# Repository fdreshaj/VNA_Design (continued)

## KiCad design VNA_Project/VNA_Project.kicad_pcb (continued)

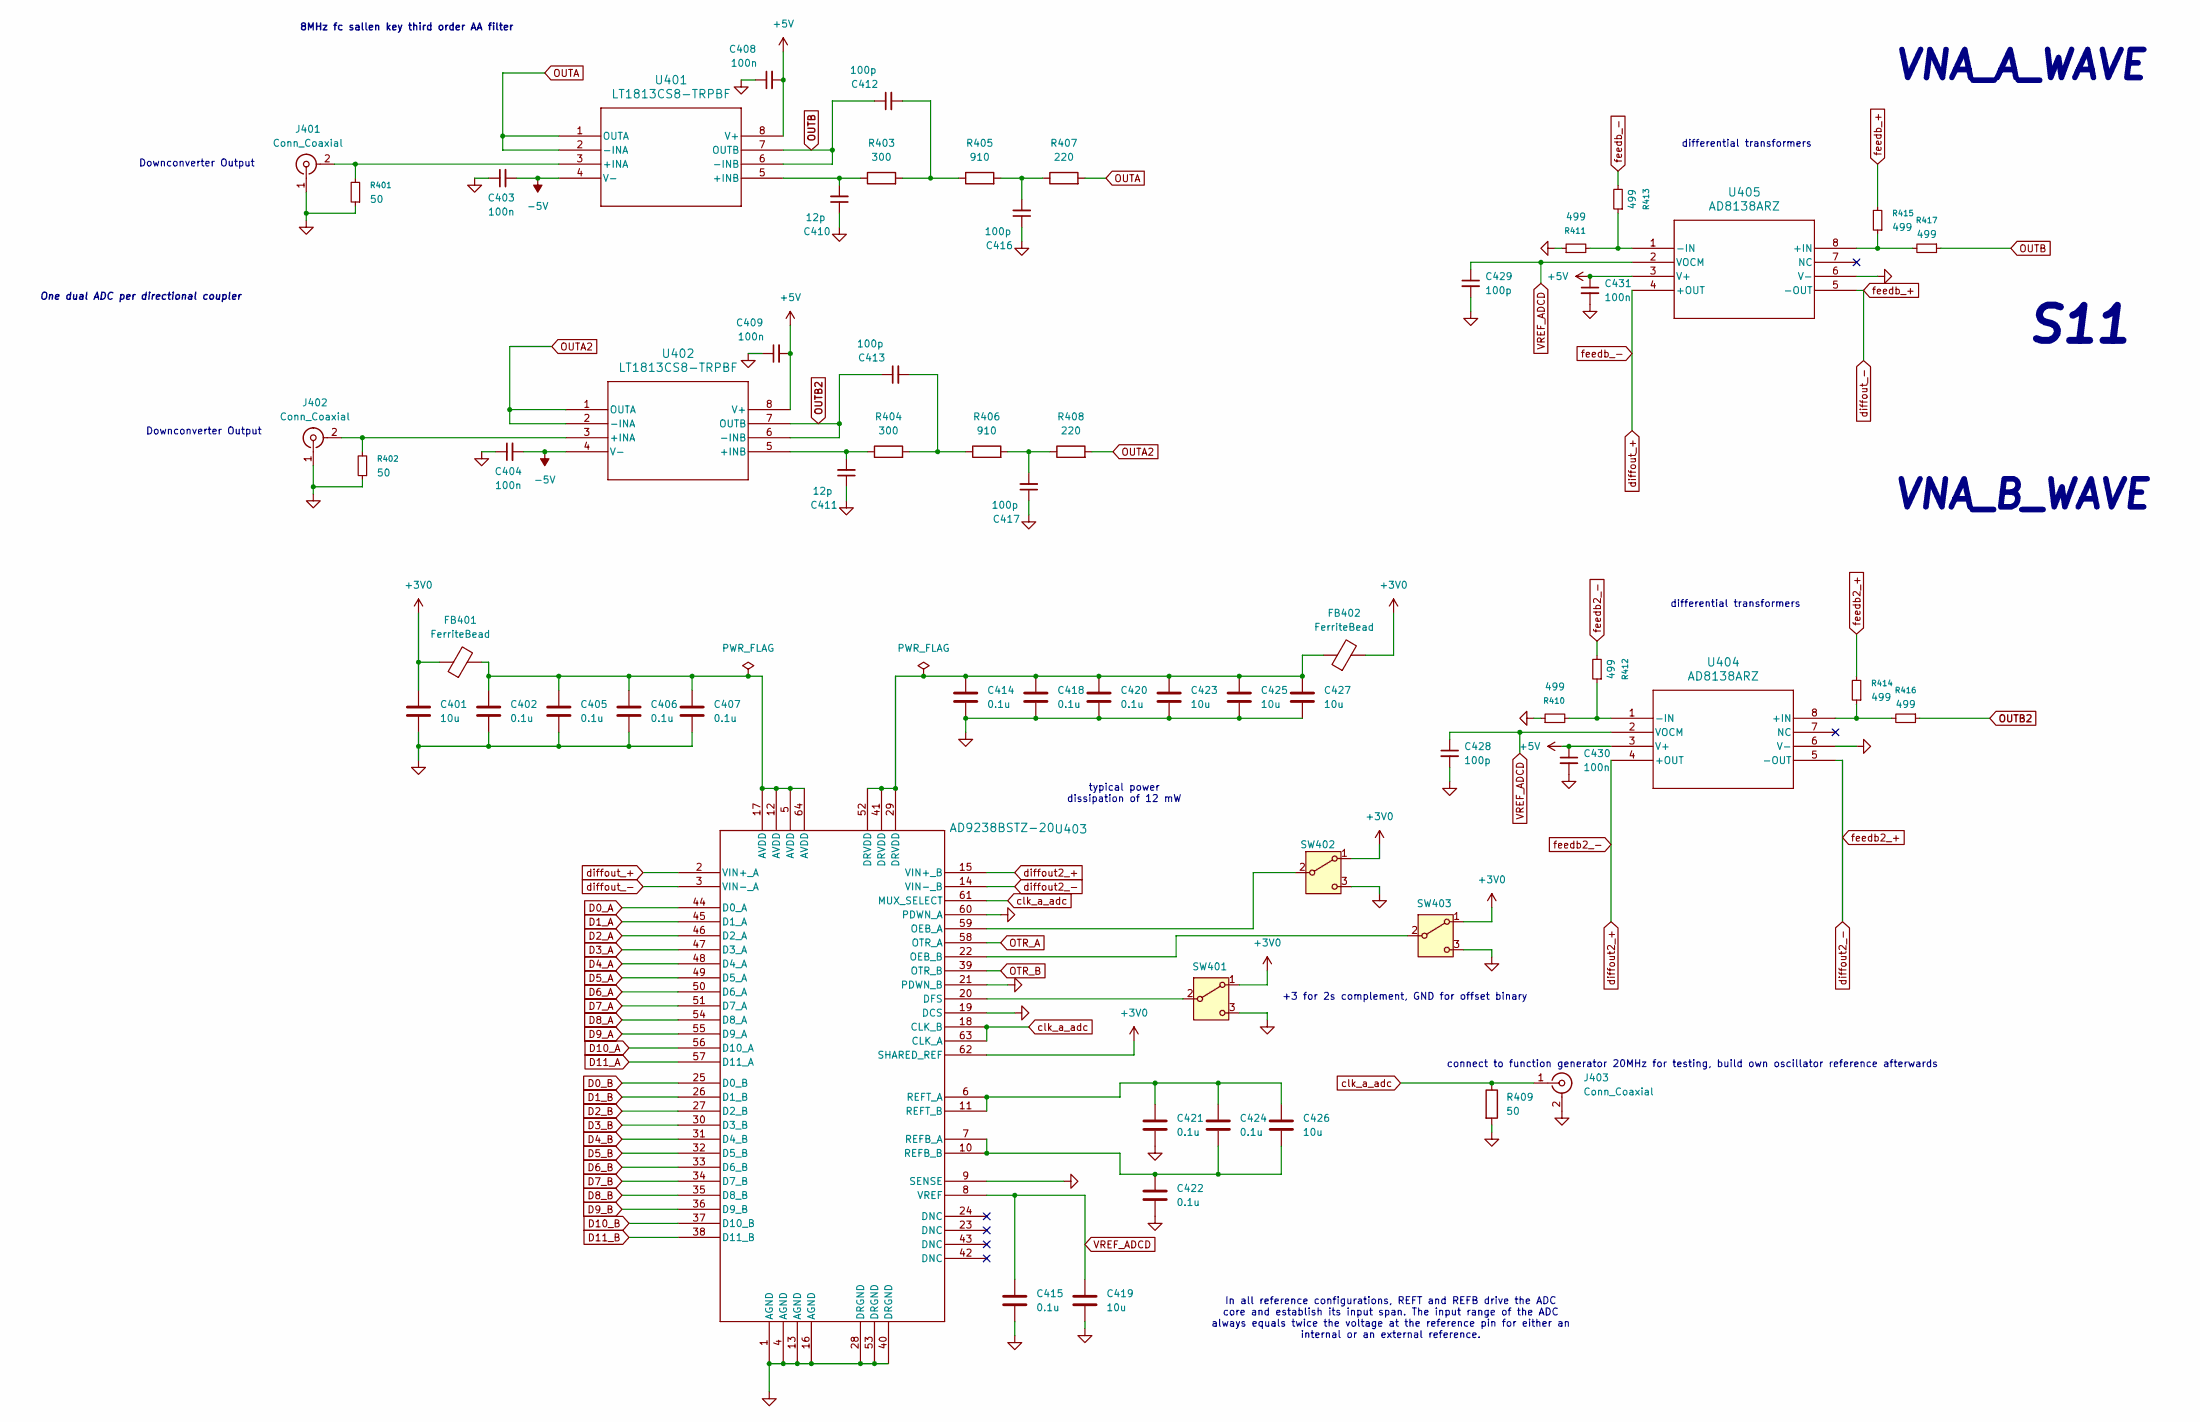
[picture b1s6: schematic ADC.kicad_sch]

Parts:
C401, C419, C423, C425, C426, C427: 10u; C_0603_1608Metric_Pad1.08x0.95mm_HandSolder
C402, C405, C406, C407, C414, C415, C418, C420, C421, C422, C424: 0.1u; C_0603_1608Metric_Pad1.08x0.95mm_HandSolder
C403, C404, C408, C409, C430, C431: 100n; C_0603_1608Metric_Pad1.08x0.95mm_HandSolder
C410, C411: 12p; C_0603_1608Metric_Pad1.08x0.95mm_HandSolder
C412, C413, C416, C417, C428, C429: 100p; C_0603_1608Metric_Pad1.08x0.95mm_HandSolder
FB401, FB402: FerriteBead; L_0603_1608Metric_Pad1.05x0.95mm_HandSolder
J401, J402, J403: Conn_Coaxial; SMA_Amphenol_901-144_Vertical
R401, R402, R409: 50; R_0603_1608Metric_Pad0.98x0.95mm_HandSolder
R403, R404: 300; R_0603_1608Metric_Pad0.98x0.95mm_HandSolder
R405, R406: 910; R_0603_1608Metric_Pad0.98x0.95mm_HandSolder
R407, R408: 220; R_0603_1608Metric_Pad0.98x0.95mm_HandSolder
R410, R411, R412, R413, R414, R415, R416, R417: 499; R_0603_1608Metric_Pad0.98x0.95mm_HandSolder
SW401, SW402, SW403: SW_SPDT; SW_Slide_SPDT_Straight_CK_OS102011MS2Q
U401, U402: LT1813CS8-TRPBF; SO-8_S_LIT-L
U403: AD9238BSTZ-20; ST_64_1_ADI
U404, U405: AD8138ARZ; R_8_ADI

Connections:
+3V0: C401.1, FB401.1, FB402.2, SW401.1 (A), SW402.1 (A), SW403.1 (A), U403.62 (SHARED_REF); also elsewhere on the board
+5V: C408.2, C409.2, C430.1, C431.1, U401.8 (V+), U402.8 (V+), U404.3 (V+), U405.3 (V+); also elsewhere on the board
-5V: C403.2, C404.2, U401.4 (V-), U402.4 (V-); also elsewhere on the board
D0_A: U403.44 (D0_A); also elsewhere on the board
D0_B: U403.25 (D0_B); also elsewhere on the board
D1_A: U403.45 (D1_A); also elsewhere on the board
D1_B: U403.26 (D1_B); also elsewhere on the board
D2_A: U403.46 (D2_A); also elsewhere on the board
D2_B: U403.27 (D2_B); also elsewhere on the board
D3_A: U403.47 (D3_A); also elsewhere on the board
D3_B: U403.30 (D3_B); also elsewhere on the board
D4_A: U403.48 (D4_A); also elsewhere on the board
D4_B: U403.31 (D4_B); also elsewhere on the board
D5_A: U403.49 (D5_A); also elsewhere on the board
D5_B: U403.32 (D5_B); also elsewhere on the board
D6_A: U403.50 (D6_A); also elsewhere on the board
D6_B: U403.33 (D6_B); also elsewhere on the board
D7_A: U403.51 (D7_A); also elsewhere on the board
D7_B: U403.34 (D7_B); also elsewhere on the board
D8_A: U403.54 (D8_A); also elsewhere on the board
D8_B: U403.35 (D8_B); also elsewhere on the board
D9_A: U403.55 (D9_A); also elsewhere on the board
D9_B: U403.36 (D9_B); also elsewhere on the board
D10_A: U403.56 (D10_A); also elsewhere on the board
D10_B: U403.37 (D10_B); also elsewhere on the board
D11_A: U403.57 (D11_A); also elsewhere on the board
D11_B: U403.38 (D11_B); also elsewhere on the board
GND: C401.2, C402.2, C403.1, C404.1, C405.2, C406.2, C407.2, C408.1, C409.1, C410.1, C411.1, C414.2, C415.2, C416.1, C417.1, C418.2, C419.2, C420.2, C421.2, C422.2, C423.2, C425.2, C427.2, C428.2, C429.2, C430.2, C431.2, J401.1 (In), J402.1 (In), J403.2 (Ext), R401.1, R402.1, R409.2, R410.1, R411.1, SW401.3 (C), SW402.3 (C), SW403.3 (C), U403.1 (AGND), U403.4 (AGND), U403.9 (SENSE), U403.13 (AGND), U403.16 (AGND), U403.19 (DCS), U403.21 (PDWN_B), U403.28 (DRGND), U403.40 (DRGND), U403.53 (DRGND), U403.60 (PDWN_A), U404.6 (V-), U405.6 (V-); also elsewhere on the board
unnamed: C402.1, C405.1, C406.1, C407.1, FB401.2, U403.5 (AVDD), U403.12 (AVDD), U403.17 (AVDD), U403.64 (AVDD)
unnamed: C412.2, R403.2, R405.1
unnamed: C413.2, R404.2, R406.1
unnamed: C414.1, C418.1, C420.1, C423.1, C425.1, C427.1, FB402.1, U403.29 (DRVDD), U403.41 (DRVDD), U403.52 (DRVDD)
unnamed: C416.2, R405.2, R407.1
unnamed: C417.2, R406.2, R408.1
unnamed: J401.2 (Ext), R401.2, U401.3 (+INA)
unnamed: J402.2 (Ext), R402.2, U402.3 (+INA)
unnamed: SW401.2 (B), U403.20 (DFS)
unnamed: SW402.2 (B), U403.59 (OEB_A)
unnamed: SW403.2 (B), U403.22 (OEB_B)
unnamed: C410.2, R403.1, U401.5 (+INB)
unnamed: C411.2, R404.1, U402.5 (+INB)
unnamed: C422.1, C424.2, C426.2, U403.7 (REFB_A), U403.10 (REFB_B)
unnamed: C421.1, C424.1, C426.1, U403.6 (REFT_A), U403.11 (REFT_B)
unnamed: R414.1, R416.2, U404.8 (+IN)
unnamed: R410.2, R412.1, U404.1 (-IN)
unnamed: R415.1, R417.2, U405.8 (+IN)
unnamed: R411.2, R413.1, U405.1 (-IN)
OTR_A: U403.58 (OTR_A); also elsewhere on the board
OTR_B: U403.39 (OTR_B); also elsewhere on the board
OUTA: R407.2, U401.1 (OUTA), U401.2 (-INA)
OUTA2: R408.2, U402.1 (OUTA), U402.2 (-INA)
OUTB: C412.1, R417.1, U401.6 (-INB), U401.7 (OUTB)
OUTB2: C413.1, R416.1, U402.6 (-INB), U402.7 (OUTB)
VREF_ADCD: C415.1, C419.1, C428.1, C429.1, U403.8 (VREF), U404.2 (VOCM), U405.2 (VOCM)
clk_a_adc: J403.1 (In), R409.1, U403.18 (CLK_B), U403.61 (MUX_SELECT), U403.63 (CLK_A)
diffout2_+: R412.2, U403.15 (VIN+_B), U404.4 (+OUT)
diffout2_-: R414.2, U403.14 (VIN-_B), U404.5 (-OUT)
diffout_+: R413.2, U403.2 (VIN+_A), U405.4 (+OUT)
diffout_-: R415.2, U403.3 (VIN-_A), U405.5 (-OUT)

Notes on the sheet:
VNA_B_WAVE
differential transformers
Downconverter Output
8MHz fc sallen key third order AA filter
connect to function generator 20MHz for testing, build own oscillator reference afterwards
+3 for 2s complement, GND for offset binary
S11
One dual ADC per directional coupler
typical power dissipation of 12 mW
In all reference configurations, REFT and REFB drive the ADC core and establish its input span. The input range of the ADC always equals twice the voltage at the reference pin for either an internal or an external reference.
VNA_A_WAVE

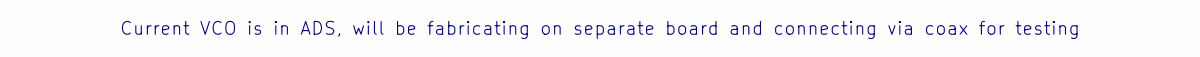
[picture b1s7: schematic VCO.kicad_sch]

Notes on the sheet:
Current VCO is in ADS, will be fabricating on separate board and connecting via coax for testing

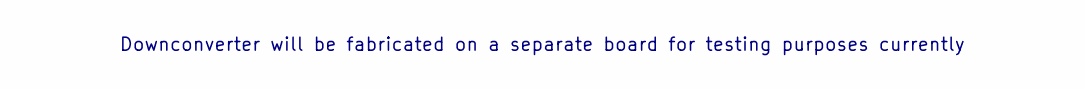
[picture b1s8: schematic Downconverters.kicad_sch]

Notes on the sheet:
Downconverter will be fabricated on a separate board for testing purposes currently

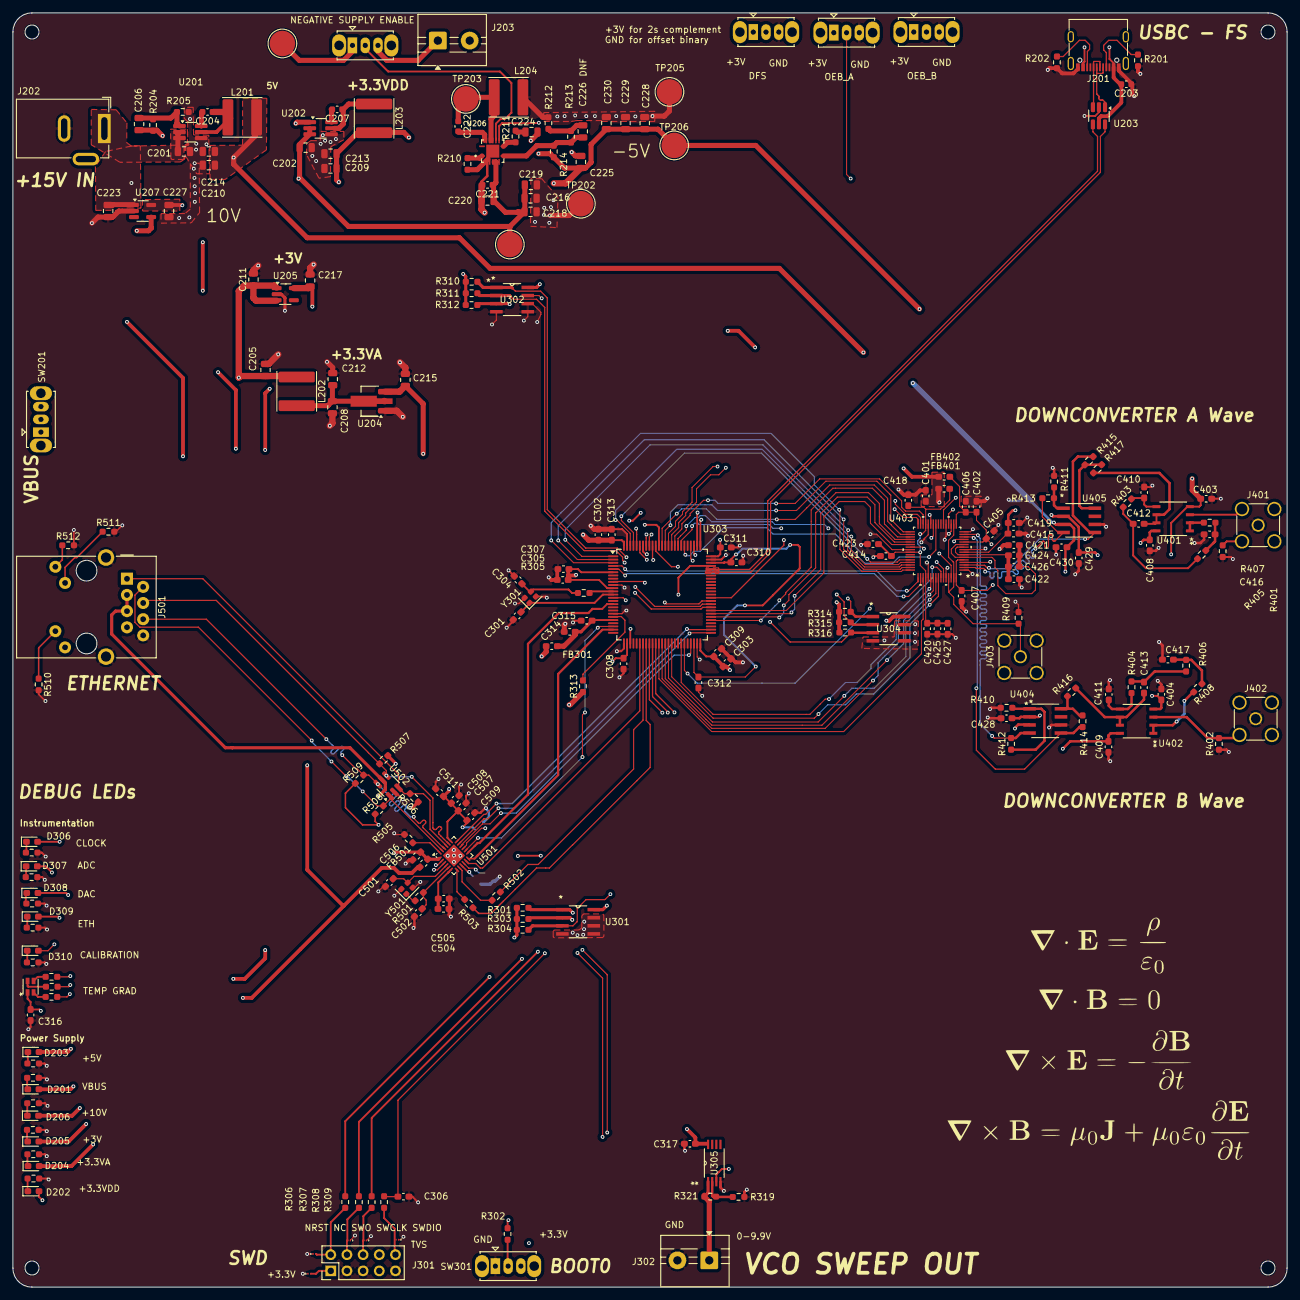
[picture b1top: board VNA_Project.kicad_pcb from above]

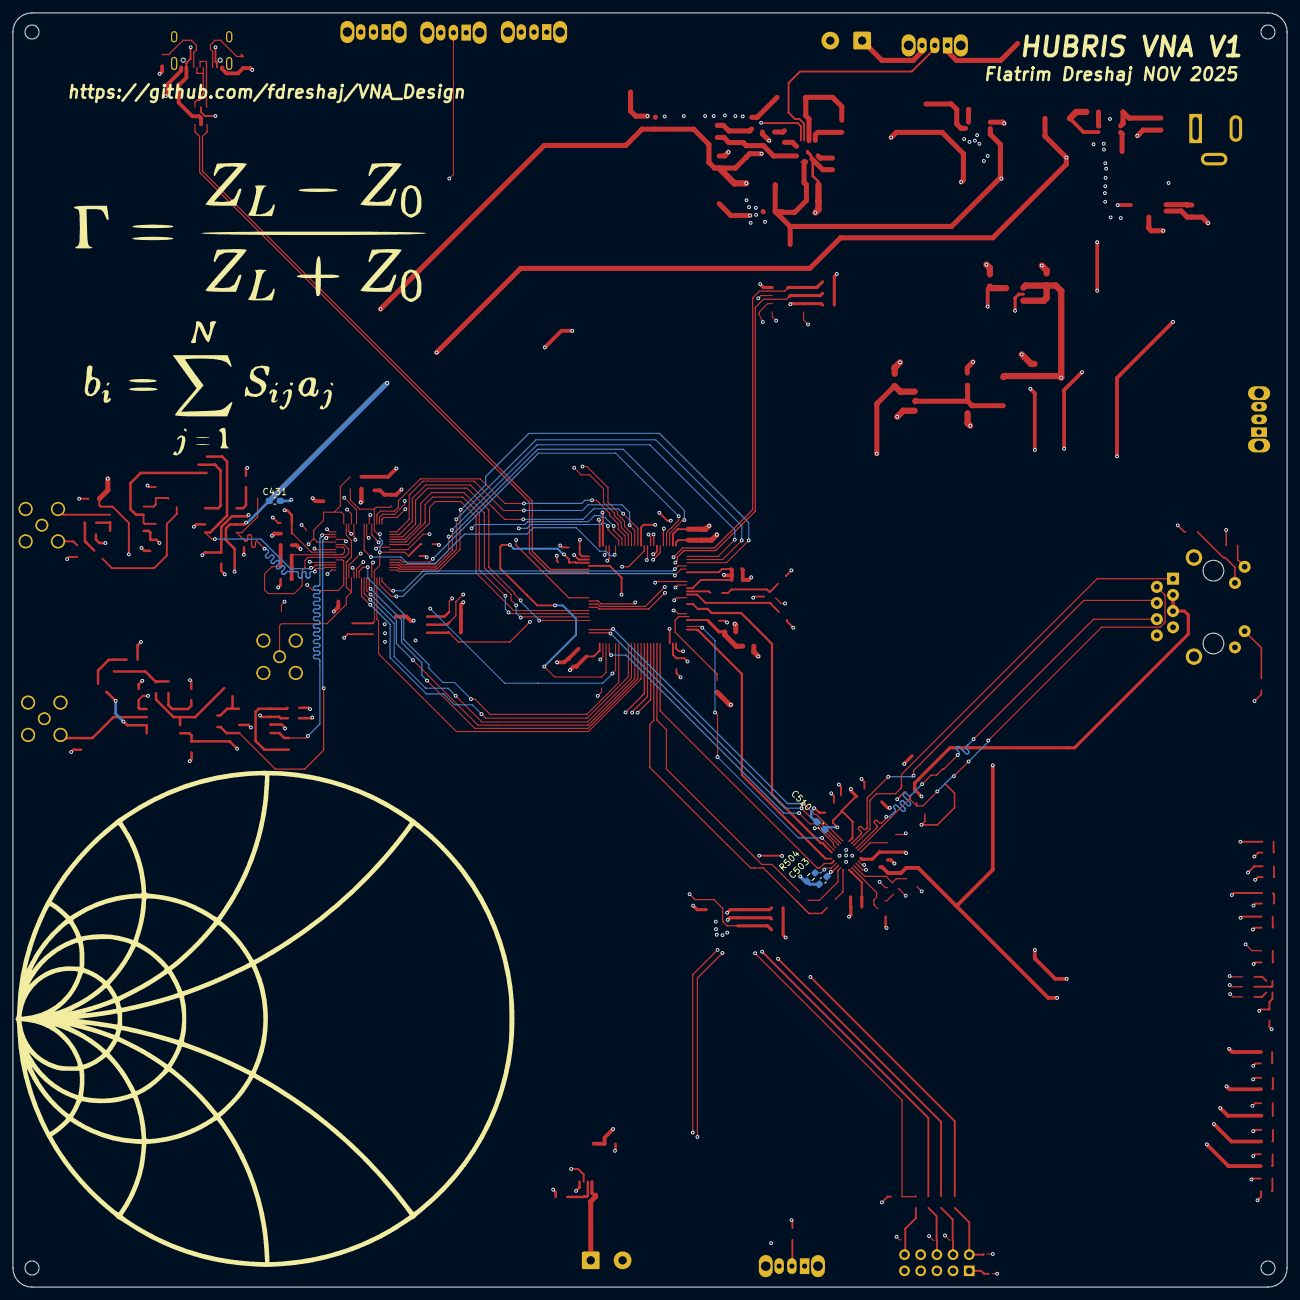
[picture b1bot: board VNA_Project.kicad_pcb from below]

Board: 6 copper layers, 200.0 x 200.0 mm, 230 parts (4 on the bottom side), 164 nets.

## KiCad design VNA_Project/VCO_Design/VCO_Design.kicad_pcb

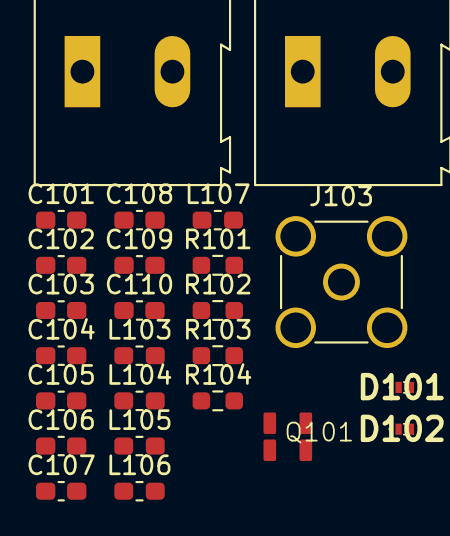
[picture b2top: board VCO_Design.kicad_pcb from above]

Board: 2 copper layers, 25 parts (0 on the bottom side), 13 nets, no tracks yet.

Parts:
C101: 22p; C_0603_1608Metric_Pad1.08x0.95mm_HandSolder
C102, C103: 100n; C_0603_1608Metric_Pad1.08x0.95mm_HandSolder
C104, C105, C108, C109, C110: 22u; C_0603_1608Metric_Pad1.08x0.95mm_HandSolder
C106: 1.2p; C_0603_1608Metric_Pad1.08x0.95mm_HandSolder
C107: 1p; C_0603_1608Metric_Pad1.08x0.95mm_HandSolder
D101, D102: D_Capacitance; SMV1247
J101, J102: Screw_Terminal_01x02; TerminalBlock_Altech_AK300-2_P5.00mm
J103: Conn_Coaxial; SMA_Amphenol_901-144_Vertical
L103: 1.1n; L_0603_1608Metric_Pad1.05x0.95mm_HandSolder
L104, L105, L106, L107: 6.8n; L_0603_1608Metric_Pad1.05x0.95mm_HandSolder
Q101: BFP620; bfptransistor
R101: 5.6k; R_0603_1608Metric_Pad0.98x0.95mm_HandSolder
R102, R104: 0.3k; R_0603_1608Metric_Pad0.98x0.95mm_HandSolder
R103: 4.4k; R_0603_1608Metric_Pad0.98x0.95mm_HandSolder

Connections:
+5V: C102.2, C103.2, J102.1, R101.1, R102.1
GND: C101.2, C102.1, C103.1, C110.1, J101.2, J102.2, J103.2 (Ext), L103.1, L104.1, L106.1, R103.2, R104.2
unnamed: C105.2, C106.1, C107.2
unnamed: C107.1, C108.2
unnamed: C108.1, D101.2 (A), L104.2
unnamed: C109.2, D101.1 (K), L105.2
unnamed: C109.1, D102.2 (A), L106.2
unnamed: C110.2, D102.1 (K), L107.2
unnamed: C104.2, C106.2, J103.1 (In), L103.2
unnamed: C101.1, R101.2, R103.1
unnamed: C104.1, R102.2
unnamed: C105.1, R104.1
VCO: J101.1, L105.1, L107.1

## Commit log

2025-09-06 initial vco research
    initial vco research
2025-09-06 VCO and Power initial designs for 600-1200MHz
    VCO and Power initial designs for 600-1200MHz
2025-09-07 Started on MCU design, for sweeping
2025-09-07 Added ESP32 MCU design
2025-09-10 ADS schematic
    Added Keysight ADS schematic, will be working on getting a simulation done by this week for the VCO
    .
2025-10-07 VCO design
    VCO design initial prototype for 2.4-2.6 GHz with quite low phase noise of -123.6 dBc at 2.45
2025-10-08 Directional Coupler Schematic Design, 2.45 GHz
2025-10-08 Dir Coupler design 2.45 GHz
2025-10-08 Create design_equations
2025-10-14 directional coupler redesign
    dir coupler redesign
2025-10-15 Replace zip archive with extracted design files
    Removed the directional_coupler_design_git_v2.zip archive and added its extracted contents to version control. This change improves transparency and enables direct tracking of individual design files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
2025-10-25 Changing from a ESP32 S3 to STM32 H7 high performance MCU for USB HS and ETH capabilities
    Changing from a ESP32 S3 to STM32 H7 high performance MCU for USB HS and ETH capabilities
2025-10-25 minor changes
    minor changes
2025-10-29 minor changes eth
    minor changes eth
2025-10-29 eth
    eth
2025-10-29 Eth done
    Eth done
2025-10-29 ADC initial
    ADC initial
2025-10-29 ADC AA filter
    ADC AA Filter
2025-11-02 adc
    adc
2025-11-03 DAC
    DAC
2025-11-03 finishing up front end
    refining Non RF front end
2025-11-03 AA filtering
    redoing AA filtering
2025-11-03 VNA V1
    FRONT END FIRST PROTOTYPE SCHEMATIC DONE
2025-11-03 footprints + initial layout shape
    footprints + initial layout shape
2025-11-04 Layout
    Layout
2025-11-10 ethernet Layout
    Ethernet Layout
2025-11-11 Clarify KiCad file updates and layout tasks
    Updated README to clarify KiCad file status and remaining work on the motherboard layout.
2025-11-28 finished Routing
    finished Routing
2025-11-28 Update README with motherboard layout changes
2025-11-28 Add images for motherboard layout in README
    Added images to the README for motherboard layout.
2025-11-28 clearance changed
    clearance changed
2025-11-28 DRC silkscreen
    fixed DRC and silkscreen
2025-11-28 Update README with new layout images
    Added additional images to the layout section.
2025-11-29 GRB BOM
    GRB BOM
2025-11-30 VCO Design
    VCO Design
2025-12-01 Update VCO_Design.kicad_sch
    vco finished,
2025-12-01 Enhance README with layout and 3D layer images
    Added additional images and layout sections to README.
2025-12-01 Add additional images to README.md
2025-12-01 gerb
    gerbers
